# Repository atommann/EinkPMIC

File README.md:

# EinkPMIC
Let there be dark!

# Intro

Let's play with the ePaper.

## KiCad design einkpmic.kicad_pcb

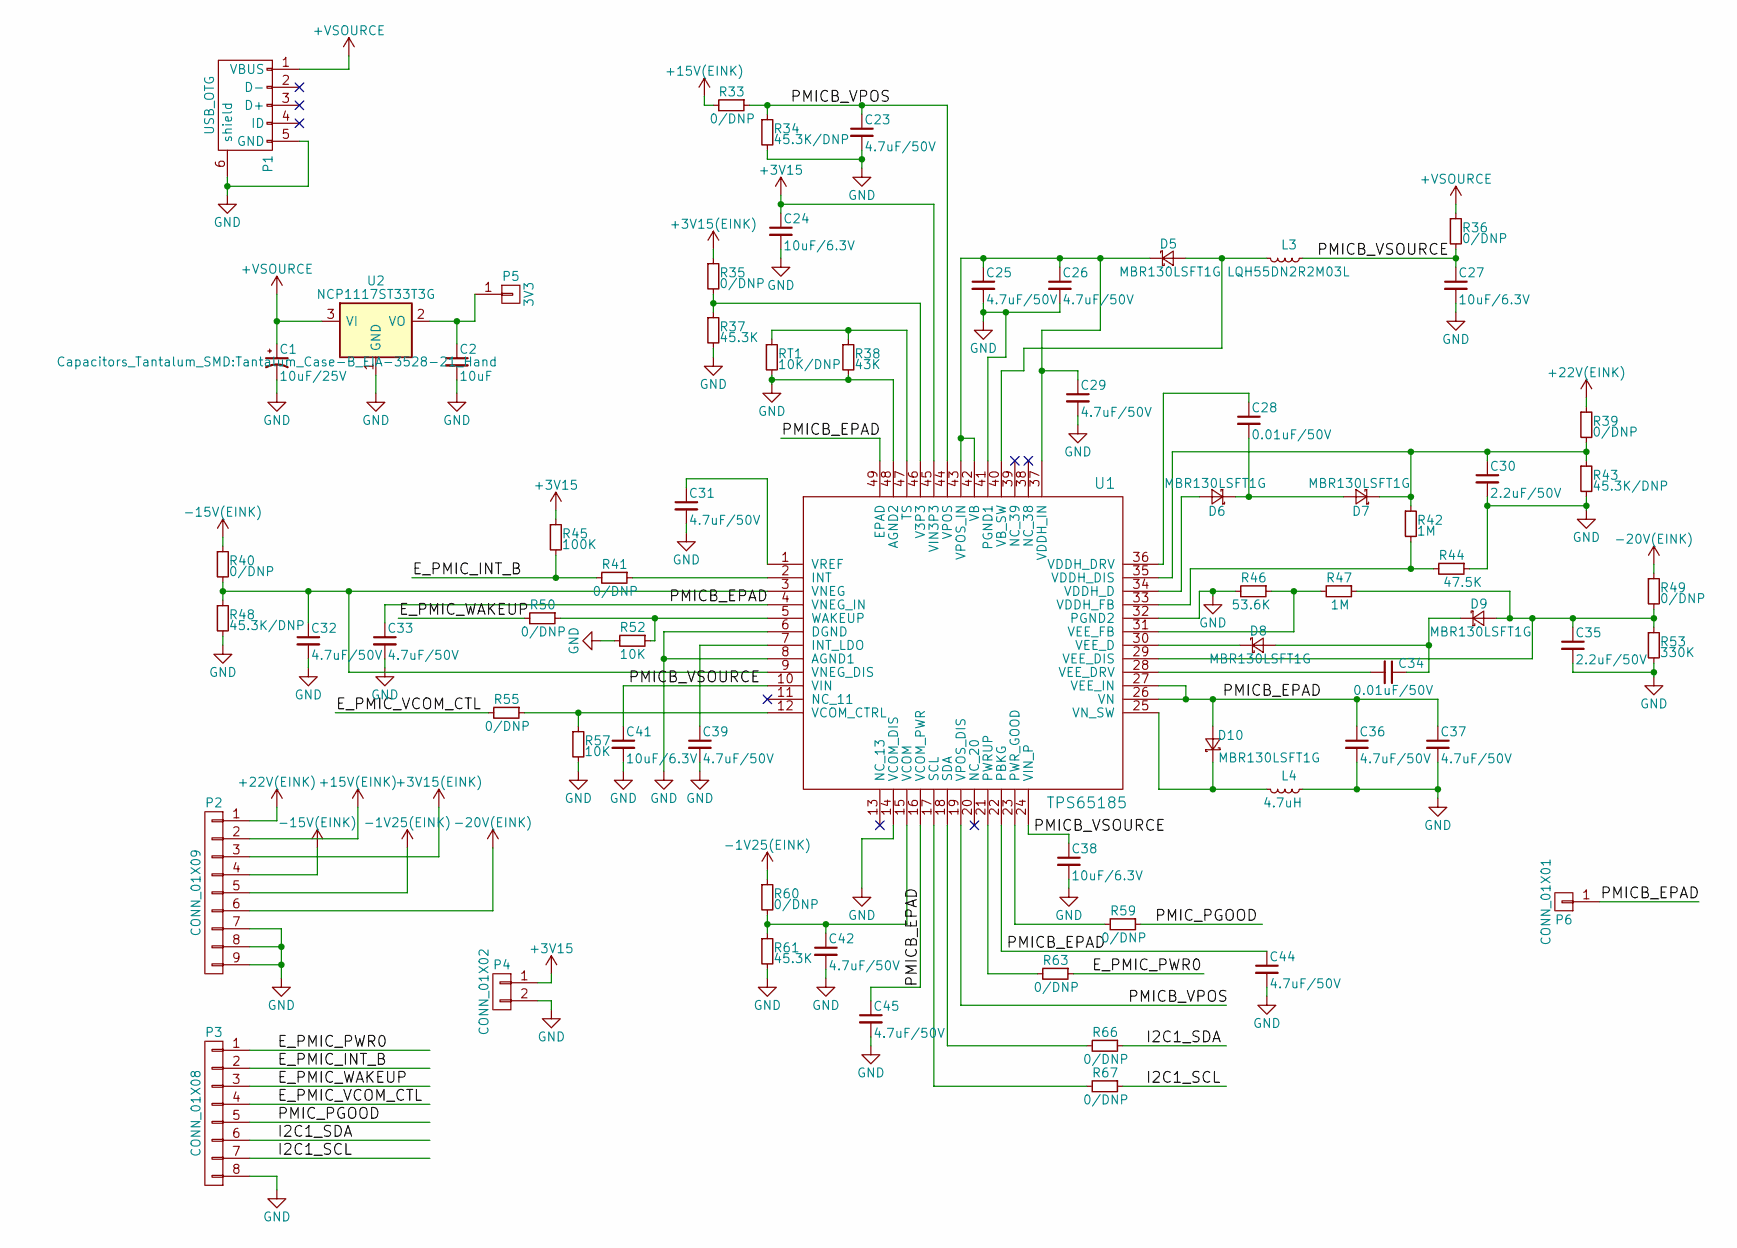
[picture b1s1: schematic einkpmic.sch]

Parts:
C1: 10uF/25V; Tantalum_Case-B_EIA-3528-21_Hand
C2: 10uF; C_0603_HandSoldering
C23, C25, C26, C29, C31, C32, C33, C36, C37, C39, C42, C44, C45: 4.7uF/50V; C_0603_HandSoldering
C24, C27, C38, C41: 10uF/6.3V; C_0603_HandSoldering
C28, C34: 0.01uF/50V; C_0603_HandSoldering
C30, C35: 2.2uF/50V; C_0603_HandSoldering
D5, D6, D7, D8, D9, D10: MBR130LSFT1G; SOD-123
L3: LQH55DN2R2M03L; Inductor_Taiyo-Yuden_NR-50xx_HandSoldering
L4: 4.7uH; Inductor_Taiyo-Yuden_NR-50xx_HandSoldering
P1: USB_OTG; USB_Micro-B
P2: CONN_01X09; CONN_2.54mm_1x9
P3: CONN_01X08; CONN_2.54mm_1x8
P4: CONN_01X02; CONN_2.54mm_1x2
P5: 3V3; CONN_2.54mm_1x1
P6: CONN_01X01; thermal
R33, R35, R36, R39, R40, R41, R49, R50, R55, R59, R60, R63, R66, R67: 0/DNP; R_0603_HandSoldering
R34, R43, R48: 45.3K/DNP; R_0603_HandSoldering
R37, R61: 45.3K; R_0603_HandSoldering
R38: 43K; R_0603_HandSoldering
R42, R47: 1M; R_0603_HandSoldering
R44: 47.5K; R_0603_HandSoldering
R45: 100K; R_0603_HandSoldering
R46: 53.6K; R_0603_HandSoldering
R52, R57: 10K; R_0603_HandSoldering
R53: 330K; R_0603_HandSoldering
RT1: 10K/DNP; R_0603_HandSoldering
U1: TPS65185; QFN-48-1EP_7x7mm_Pitch0.5mm
U2: NCP1117ST33T3G; SOT-223

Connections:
+3V15: C24.1, P4.1, R45.1, U1.45 (VIN3P3)
+3V15(EINK): P2.3, R35.1
+15V(EINK): P2.2, R33.2
+22V(EINK): P2.1, R39.1
+VSOURCE: C1.1, P1.1 (VBUS), R36.1, U2.3 (VI)
-1V25(EINK): P2.5, R60.1
-15V(EINK): P2.4, R40.1
-20V(EINK): P2.6, R49.1
/E_PMIC_INT_B: P3.2, R41.2, R45.2
/E_PMIC_PWR0: P3.1, R63.1
/E_PMIC_VCOM_CTL: P3.4, R55.2
/E_PMIC_WAKEUP: P3.3, R50.2
/I2C1_SCL: P3.7, R67.1
/I2C1_SDA: P3.6, R66.1
/PMICB_EPAD: C33.1, C36.1, C37.1, C44.1, C45.1, D10.2 (A), P6.1, U1.4 (VNEG_IN), U1.16 (VCOM_PWR), U1.22 (PBKG), U1.26 (VN), U1.27 (VEE_IN), U1.49 (EPAD)
/PMICB_VPOS: C23.1, R33.1, R34.1, U1.19 (VPOS_DIS), U1.44 (VPOS)
/PMICB_VSOURCE: C27.1, C38.1, C41.1, L3.1, R36.2, U1.10 (VIN), U1.24 (VIN_P)
/PMIC_PGOOD: P3.5, R59.1
GND: C1.2, C2.2, C23.2, C24.2, C25.2, C26.2, C27.2, C29.2, C30.2, C31.2, C32.2, C33.2, C35.2, C36.2, C37.2, C38.2, C39.2, C41.2, C42.2, C44.2, C45.2, L4.1, P1.5 (GND), P1.6 (shield), P2.7, P2.8, P2.9, P3.8, P4.2, R34.2, R37.2, R38.2, R43.2, R44.1, R46.2, R48.2, R52.2, R53.2, R57.2, R61.2, RT1.2, U1.6 (DGND), U1.8 (AGND1), U1.14 (VCOM_DIS), U1.32 (PGND2), U1.41 (PGND1), U1.48 (AGND2), U2.1 (GND)
unnamed: C2.1, P5.1, U2.2 (VO)
unnamed: C25.1, C26.1, C29.1, D5.1 (K), U1.37 (VDDH_IN), U1.42 (VB), U1.43 (VPOS_IN)
unnamed: C28.1, U1.36 (VDDH_DRV)
unnamed: C28.2, D6.1 (K), D7.2 (A)
unnamed: C30.1, D7.1 (K), R39.2, R42.1, R43.1, U1.35 (VDDH_DIS)
unnamed: C31.1, U1.1 (VREF)
unnamed: C32.1, R40.2, R48.1, U1.3 (VNEG), U1.9 (VNEG_DIS)
unnamed: C34.1, D8.2 (A), D9.1 (K)
unnamed: C34.2, U1.28 (VEE_DRV)
unnamed: C35.1, D9.2 (A), R47.1, R49.2, R53.1, U1.29 (VEE_DIS)
unnamed: C39.1, U1.7 (INT_LDO)
unnamed: C42.1, R60.2, R61.1, U1.15 (VCOM)
unnamed: D5.2 (A), L3.2, U1.40 (VB_SW)
unnamed: D6.2 (A), U1.34 (VDDH_D)
unnamed: D8.1 (K), U1.30 (VEE_D)
unnamed: D10.1 (K), L4.2, U1.25 (VN_SW)
unnamed: R35.2, R37.1, U1.46 (V3P3)
unnamed: R38.1, RT1.1, U1.47 (TS)
unnamed: R41.1, U1.2 (INT)
unnamed: R42.2, R44.2, U1.33 (VDDH_FB)
unnamed: R46.1, R47.2, U1.31 (VEE_FB)
unnamed: R50.1, R52.1, U1.5 (WAKEUP)
unnamed: R55.1, R57.1, U1.12 (VCOM_CTRL)
unnamed: R59.2, U1.23 (PWR_GOOD)
unnamed: R63.2, U1.21 (PWRUP)
unnamed: R66.2, U1.18 (SDA)
unnamed: R67.2, U1.17 (SCL)

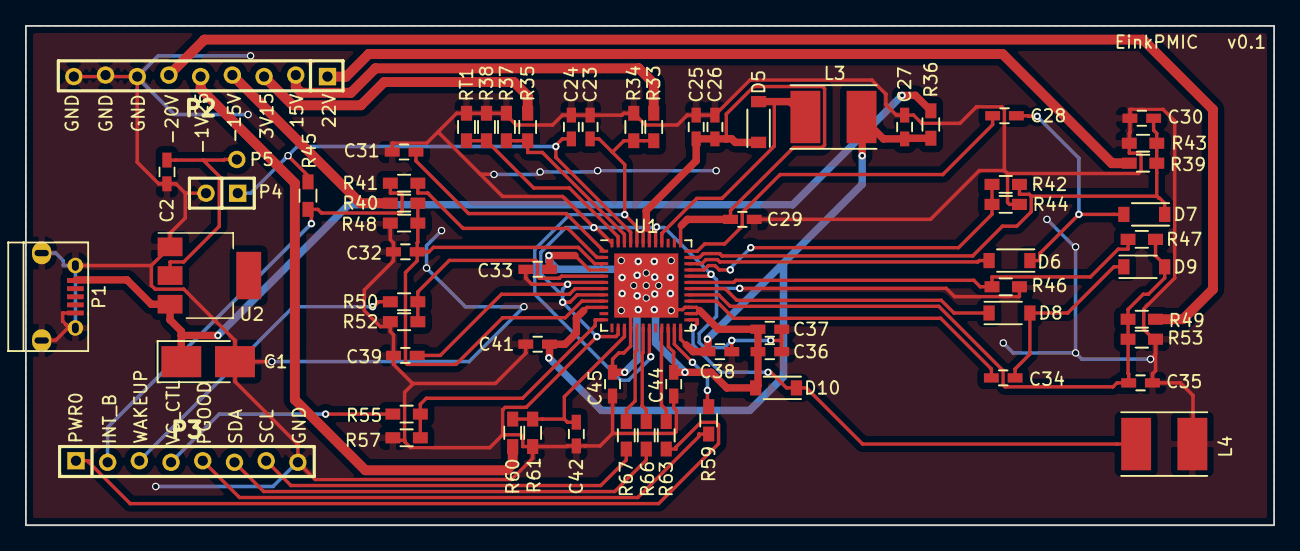
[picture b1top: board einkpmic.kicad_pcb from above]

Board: 2 copper layers, 100.0 x 40.0 mm, 68 parts (1 on the bottom side), 46 nets.

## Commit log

2017-02-26 init
2017-02-26 update sch
2017-02-27 update footprint
2017-03-02 update pcb
2017-03-03 update pdf
